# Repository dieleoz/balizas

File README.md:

# Baliza — Señal Vial «30 CUANDO ACTIVADA» (v3.3)

Control inteligente de la **luz intermitente de una señal de tránsito** instalada frente a zonas escolares.
Cuando la luz titila a **1.0 Hz** (500 ms ON / 500 ms OFF), el límite de **30 km/h está vigente legalmente**. El resto del día la señal permanece apagada.

El horario en el que debe titilar **está grabado físicamente en la placa metálica de la señal**:
* **Mañana:** 06:00 am a 09:00 am
* **Mediodía:** 11:30 am a 01:30 pm (13:30)
* **Tarde:** 03:00 pm (15:00) a 04:30 pm (16:30)

---

## 🏗️ Arquitectura del Sistema

```mermaid
flowchart LR
    APP["📱 App Android<br/>IT VIAL 30 v3.3<br/>Baliza_v3.3.apk"] -->|"Bluetooth SPP 9600 8N1<br/>Tramas ¿...?"| BT["Módulo Bluetooth<br/>JDY-31 / SIG0109A"]
    BT -->|"RC6 TX · RC7 RX"| PIC["PIC18F2550 (C99)<br/>Flash: 53.1% · RAM: 27.7%"]
    RTC["DS1307 + Pila CR2032<br/>Hora, Fecha y Calendario"] <-->|"I2C (Anti-Bloqueo)"| PIC
    PIC -->|"LATC2"| LUZ["💡 Foco Ámbar (1.0 Hz)"]
    PIC -->|"LATC1"| BUZ["Buzzer"]
    PIC -->|"AN1 (ADC)"| BAT["🔋 Batería 12V / Panel"]
    PIC -->|"0x00-0x5F"| EE["💾 EEPROM (Alarmas, Cortes, Nombre OTA)"]
```

## La v3.3 es una pareja, y solo vale junta

**La v3.3 son dos ficheros que se probaron juntos contra una señal real.** Confirmado por el
responsable el 22-ago-2026. No se mezclan con nada de otra procedencia:

| | Fichero | Tamaño | SHA-256 |
|---|---|---|---|
| **Firmware** | [`1 Firmware/Doc mplabx/build_xc8/main.hex`](1%20Firmware/Doc%20mplabx/build_xc8/main.hex) | 59.577 B | `c14b4350d960ce46c716d398f357acdee21f05660ef47c0ea61a7d513b8539c5` |
| **App** | [`1 Firmware/Baliza_v3.3.apk`](1%20Firmware/Baliza_v3.3.apk) | 3.859.625 B | `9c37d599deb995b0fa606d65b5e7fa7e813a08314535f9ba1959b3524d391a87` |

> ### ⚠️ Hay otro `.hex` con nombre de entregable que NO es este
>
> `BALIZA_18F2550_V1_CORREGIDO.hex` —tanto el de `1 Firmware/` como **el que hay dentro de
> `Release_v3.3/Binarios/`**— es un binario **distinto**: 49.068 B, `048856fc…`. No es el que
> funcionó. El nombre engaña justo donde más caro sale, porque está dentro de la carpeta de
> release y cualquiera lo tomaría por el bueno. **Antes de grabar, se comprueba el SHA-256, no
> el nombre del fichero.**

| Parámetro | Valor |
|---|---|
| **Microcontrolador** | **Microchip PIC18F2550** a 20.0 MHz (HS) |
| **Compilador Firmware** | **C99** (`--std=c99`). ⚠️ **La versión exacta de XC8 de este binario no está registrada**: la carpeta `build_xc8/` no conserva el `.map`. Ver ROADMAP, pendiente 5 |
| **Binario que corre HOY en la calle** | Sin confirmar — ver ROADMAP, pendiente 3 |
| **Cobertura de Pruebas** | **78 de 78 · PASS**, medido el **22-ago-2026** con `python "4 Simulador/correr.py"` |
| **Comprobación de interfaz** | **PASS** — contraste WCAG, áreas táctiles, responsive y **controles muertos**, con `comprobar_ui.py`. **No sustituye a verla en un teléfono** |

---

## Las mejoras de hoy: candidatas a la proxima version

Sobre la v3.3 hay **40 commits del 22-ago-2026** con trabajo real: saneamiento de la ISR,
aritmetica de punto fijo en vez de float, timeouts en I2C y UART, telemetria de bateria,
contador de cortes, nombre por el aire (OTA), autodiagnostico en la App y exportacion del
certificado. De ahi salen otros dos binarios:

| | Fichero | Tamano | SHA-256 (12) |
|---|---|---|---|
| Firmware | `1 Firmware/BALIZA_18F2550_V1_CORREGIDO.hex` | 49.201 B | `61e0441df8ce` |
| App | `7 sw apk/Baliza_IT_VIAL_30_v3.4.apk` | 4.570.283 B | `9864125aba51` |

**Son la base de la proxima version, no una version.** Tres cosas tienen que pasar antes de
que puedan llamarse v3.4 y salir a campo:

1. **Funcional tiene que revisar las funciones nuevas.** Ninguna lo ha hecho todavia.
2. ~~Incrementar el `versionCode`.~~ **HECHO el 22-ago-2026.** `build.gradle` esta en
   `versionCode 34` / `versionName "3.4"` y el APK se **recompilo**, asi que ahora se declara
   de verdad como 3.4 y Android si ofrece la actualizacion sobre una v3.3 instalada.
   (El tamano del APK varia entre compilaciones sin que cambie el contenido: es solo
   compresion. Comparar el contenido, no el tamano.)
3. **Hay que probar la pareja junta contra una senal real**, como se hizo con la v3.3. El
   firmware nuevo y la App nueva no se han validado juntos en campo.

Mientras tanto, **lo que se instala en campo es la v3.3**, y las dos cosas no se mezclan: la
App v3.3 con el `.hex` de la v3.3.

## Funcionalidades de la v3.3

Segun `Release_v3.3/LEEME_RELEASE_v3.3.md`, la v3.3 lleva:

**Firmware** (`main.hex`, 59.577 B)

1. **Cadencia reglamentaria de 1.0 Hz** - 500 ms encendido / 500 ms apagado.
2. **Mapeo de pines corregido:** buzzer en `RC1`, foco LED en `RC2`, pulsador en `RC0`.
3. **Parser serie protegido** contra tramas truncadas y caracteres NUL.
4. **Telemetria de bateria 12 V** por el canal ADC `AN1`.
5. **Contador de cortes de energia en EEPROM** (`0x36-0x37`).

**App** (`Baliza_v3.3.apk`, 3.859.625 B)

6. **1-Toque** que graba tres franjas FIJAS (06:00-09:00, 11:30-13:30, 15:00-16:30 L-V) — las de un colegio concreto. Sustituido en la candidata por la tarjeta «Horario de esta placa».
7. **Test de luz de 2 minutos** a 1.0 Hz con apagado rapido.
8. **Tema oscuro de alto contraste** para visibilidad diurna bajo sol.

> **Lo que NO esta en la v3.3:** el nombre por el aire (OTA), el certificado por WhatsApp y el
> semaforo de autodiagnostico. Esas son funciones de la compilacion de trabajo llamada «v3.4»
> y **no han pasado por funcional**. Si algun manual las describe como disponibles, el manual
> va por delante de lo aprobado.

---

## 🧪 Pruebas, Simulación y Emulador Web

Para verificar la compuerta de calidad o correr el simulador interactivo:

```bash
# 1. Arnés de 58 pruebas unitarias, estrés de 100k ciclos y 6 meses continuos:
python "4 Simulador/correr.py"

# 2. Suite automatizada End-to-End paso a paso (Headless):
python "4 Simulador/test_suite_e2e.py"

# 3. Emulador Web Interactivo conectado al Microcontrolador en C:
python "4 Simulador/servidor_interactivo.py"
# Abrir en el navegador: http://localhost:8080
```

---

### Qué NO cubren esas comprobaciones

El arnés compila los `.c` reales del firmware y los ejercita en el PC, pero **no toca un solo
pin**. Verde aquí no es entregable y no autoriza a grabar. En concreto no dice nada de:

* **El ADC.** Desde el 22-ago-2026 **sí lo cubre en parte** (bloque `I` del arnés), y lo
  primero que midió es que **la baliza no mide la temperatura**: el estado que la lee es
  código muerto, nadie transiciona a él. **La telemetría de batería (`AN1`) no está afectada
  y funciona.** Detalle en [`ROADMAP.md`](ROADMAP.md).
* **El I²C y el DS1307.** El reloj simulado siempre responde. Una pila `CR2032` agotada o unas
  pull-ups mal no existen en el simulador.
* **Que el módulo Bluetooth empareje.** Al arnés se le meten las tramas directamente.
* **Que el horario grabado coincida con la chapa atornillada a esa señal.** Esto es lo que más
  importa y **solo lo puede comprobar una persona con la señal delante**.

---

## 📚 Documentación Oficial y Manuales

* 📱 **Instalador de campo (v3.3, el aprobado):** [`1 Firmware/Baliza_v3.3.apk`](1%20Firmware/Baliza_v3.3.apk)
* 🔧 **Compilacion de trabajo (NO aprobada):** [`7 sw apk/Baliza_IT_VIAL_30_v3.4.apk`](7%20sw%20apk/Baliza_IT_VIAL_30_v3.4.apk)
* 🔧 **Compilar la app (cadena, dependencias, trampas):** [`Manuales/COMPILAR_APP.md`](Manuales/COMPILAR_APP.md)
* 📖 **Manual de Usuario de la App:** [`Manuales/MANUAL_USUARIO_APP.md`](Manuales/MANUAL_USUARIO_APP.md)
* ⚙️ **Manual Técnico del Firmware C99:** [`Manuales/MANUAL_TECNICO_FIRMWARE_C99.md`](Manuales/MANUAL_TECNICO_FIRMWARE_C99.md)
* 📜 **Certificado Oficial de Calibración y Pruebas:** [`Manuales/CERTIFICADO_FIRMWARE_v3.4.md`](Manuales/CERTIFICADO_FIRMWARE_v3.4.md)
* 🗺️ **Gestión de Múltiples Señales y Nombres OTA:** [`Manuales/GESTION_MULTISEÑALES_Y_NOMBRES.md`](Manuales/GESTION_MULTISE%C3%91ALES_Y_NOMBRES.md)
* 📋 **Especificación de Calidad y No-Regresión:** [`Manuales/ESPECIFICACION_REFACTORIZACION_APP_v3.4.md`](Manuales/ESPECIFICACION_REFACTORIZACION_APP_v3.4.md)
* 🩺 **Guía de Diagnóstico y Logs de Soporte:** [`Manuales/GUIA_DIAGNOSTICO_Y_LOGS_SOPORTE.md`](Manuales/GUIA_DIAGNOSTICO_Y_LOGS_SOPORTE.md)
* 🏛️ **Dictamen del Comité Técnico:** [`Manuales/DICTAMEN_COMITE_TECNICO_MULTIDISCIPLINARIO.md`](Manuales/DICTAMEN_COMITE_TECNICO_MULTIDISCIPLINARIO.md)
* ⚖️ **Base normativa (Manual de Señalización Vial):** [`Manuales/NORMATIVA.md`](Manuales/NORMATIVA.md)
* 🗺️ **Hoja de Ruta (Roadmap):** [`ROADMAP.md`](ROADMAP.md)

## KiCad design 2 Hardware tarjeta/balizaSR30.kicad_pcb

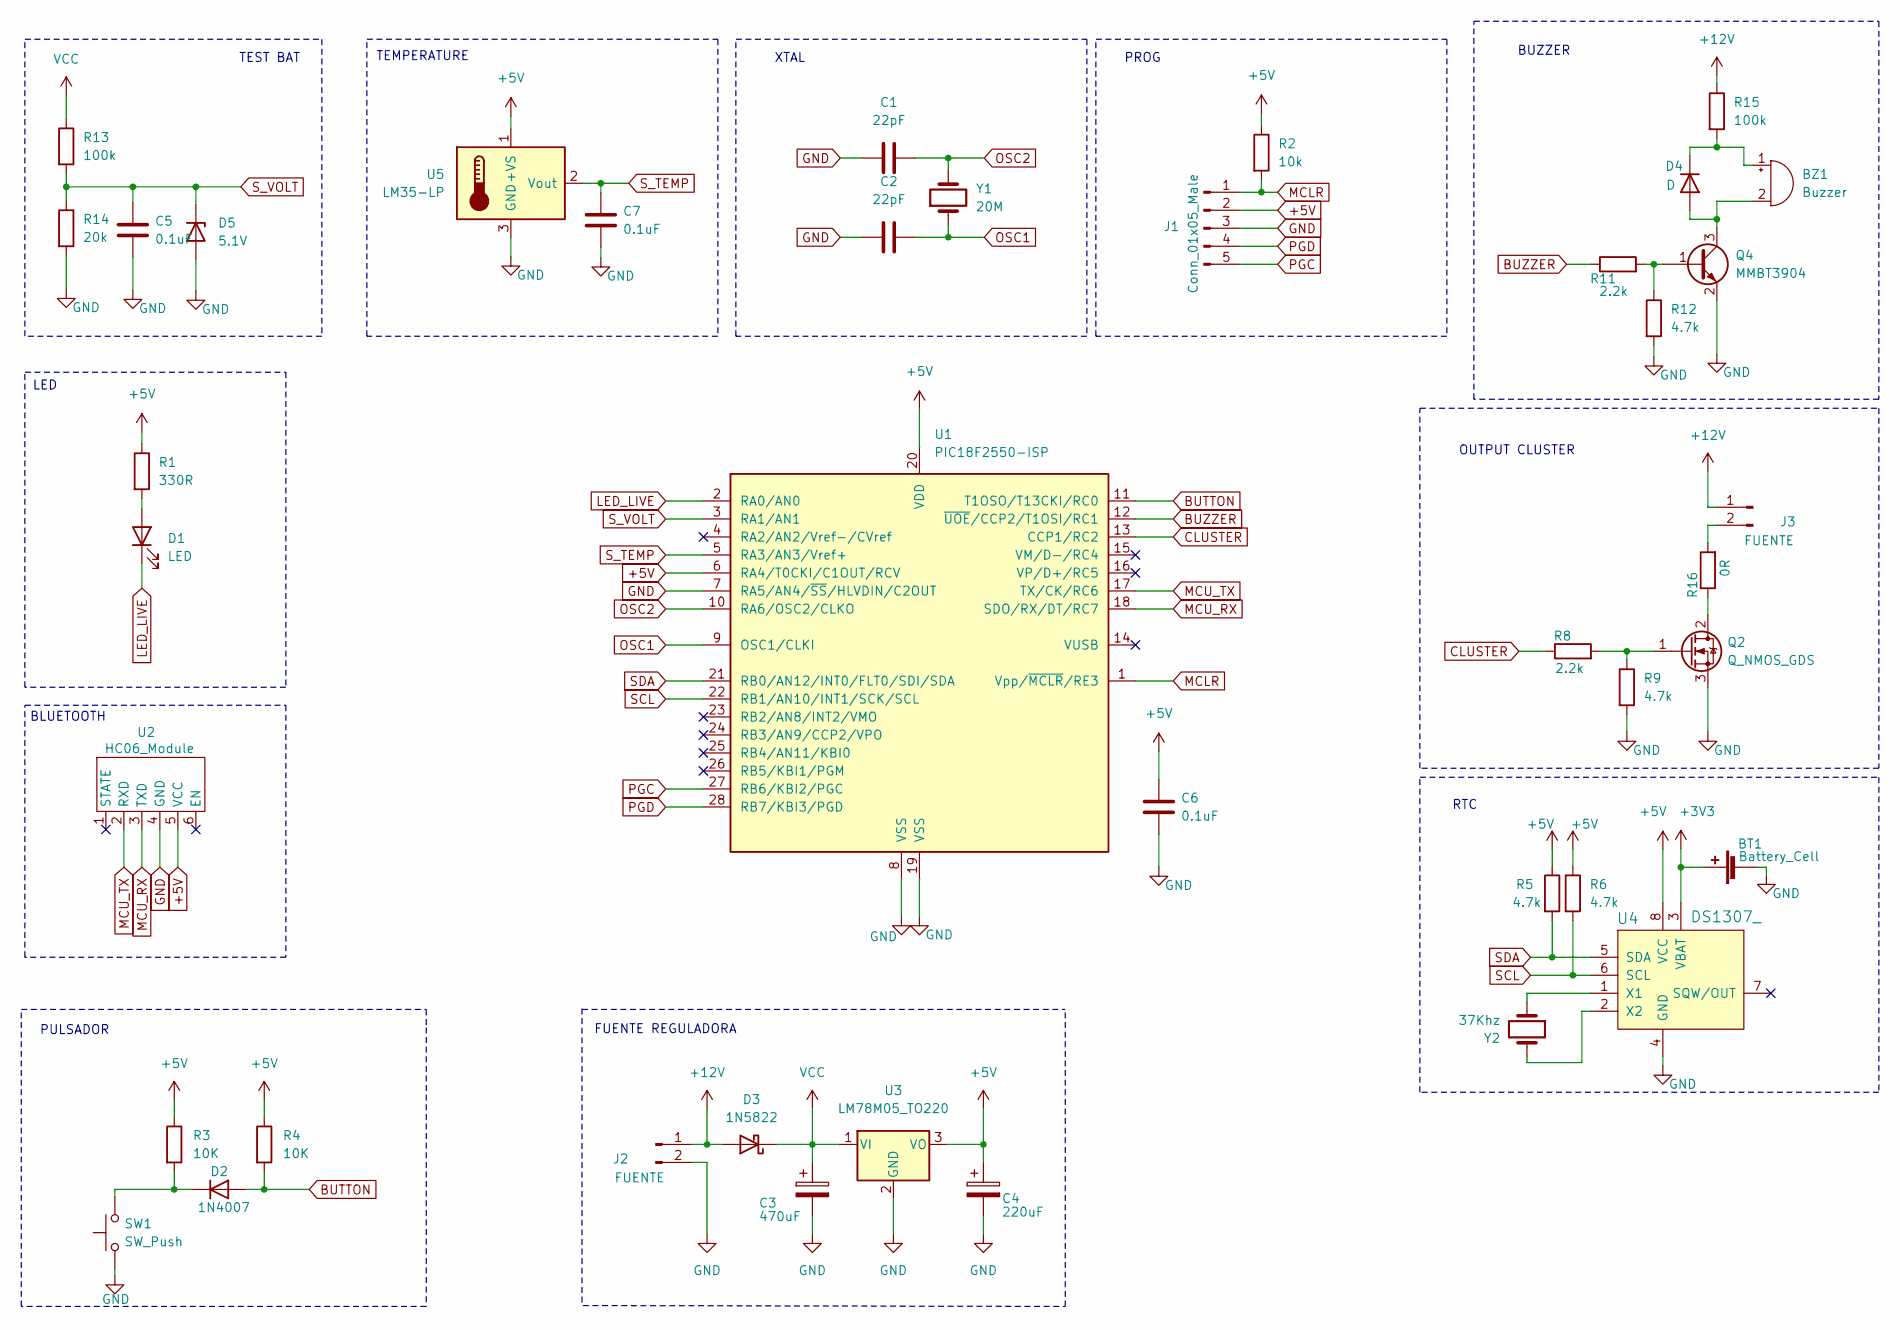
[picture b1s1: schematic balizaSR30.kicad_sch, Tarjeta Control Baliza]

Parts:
BT1: Battery_Cell; BatteryHolder_Keystone_103_1x20mm
BZ1: Buzzer; Buzzer_12x9.5RM7.6
C1, C2: 22pF; C_0805_2012Metric
C3: 470uF; CP_Radial_D8.0mm_P2.50mm
C4: 220uF; CP_Radial_D8.0mm_P2.50mm
C5, C6, C7: 0.1uF; C_0805_2012Metric
D1: LED; LED_D3.0mm
D2: 1N4007; D_DO-41_SOD81_P7.62mm_Horizontal
D3: 1N5822; D_DO-201AD_P15.24mm_Horizontal
D4: D; D_A-405_P7.62mm_Horizontal
D5: 5.1V; D_DO-34_SOD68_P7.62mm_Horizontal
J1: Conn_01x05_Male; PinHeader_1x05_P2.54mm_Vertical
J2, J3: FUENTE; Molex_KK-396_5273-02A_1x02_P3.96mm_Vertical
Q2: Q_NMOS_GDS; TO-220-3_Horizontal_TabDown
Q4: MMBT3904; SOT-23
R1: 330R; R_1206_3216Metric
R2: 10k; R_1206_3216Metric
R3, R4: 10K; R_1206_3216Metric
R5, R6, R9, R12: 4.7k; R_1206_3216Metric
R8, R11: 2.2k; R_1206_3216Metric
R13, R15: 100k; R_1206_3216Metric
R14: 20k; R_1206_3216Metric
R16: 0R; R_2010_5025Metric
SW1: SW_Push; SW_PUSH_6mm_H4.3mm
U1: PIC18F2550-ISP; DIP-28_W7.62mm
U2: HC06_Module; HC06
U3: LM78M05_TO220; TO-220-3_Horizontal_TabDown
U4: DS1307_; DIP-8_W7.62mm; MPN DS1307+; Digi-Key_PN DS1307+-ND
U5: LM35-LP; TO-92L_Inline_Wide
Y1: 20M; Crystal_HC18-U_Vertical
Y2: 37Khz; Crystal_AT310_D3.0mm_L10.0mm_Horizontal

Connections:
+3V3: BT1.1 (+), U4.3 (VBAT)
+5V: C4.1, C6.1, J1.2, R1.1, R2.1, R3.1, R4.1, R5.1, R6.1, U1.6 (RA4/T0CKI/C1OUT/RCV), U1.20 (VDD), U2.5 (VCC), U3.3 (VO), U4.8 (VCC), U5.1 (+VS)
+12V: D3.2 (A), J2.1, J3.1, R15.1
BUTTON: D2.2 (A), R4.2, U1.11 (T1OSO/T13CKI/RC0)
BUZZER: R11.1, U1.12 (~UOE/CCP2/T1OSI/RC1)
CLUSTER: R8.1, U1.13 (CCP1/RC2)
GND: BT1.2 (-), C1.1, C2.1, C3.2, C4.2, C5.2, C6.2, C7.2, D5.2 (A), J1.3, J2.2, Q2.3 (S), Q4.2 (E), R9.2, R12.2, R14.2, SW1.1, U1.7 (RA5/AN4/~SS/HLVDIN/C2OUT), U1.8 (VSS), U1.19 (VSS), U2.4 (GND), U3.2 (GND), U4.4 (GND), U5.3 (GND)
LED_LIVE: D1.1 (K), U1.2 (RA0/AN0)
MCLR: J1.1, R2.2, U1.1 (Vpp/~MCLR/RE3)
MCU_RX: U1.18 (SDO/RX/DT/RC7), U2.3 (TXD)
MCU_TX: U1.17 (TX/CK/RC6), U2.2 (RXD)
unnamed: BZ1.2 (+), D4.2 (A), Q4.3 (C)
unnamed: BZ1.1 (-), D4.1 (K), R15.2
unnamed: D1.2 (A), R1.2
unnamed: D2.1 (K), R3.2, SW1.2
unnamed: J3.2, R16.2
unnamed: Q2.2 (D), R16.1
unnamed: Q2.1 (G), R8.2, R9.1
unnamed: Q4.1 (B), R11.2, R12.1
unnamed: U4.1 (X1), Y2.1
unnamed: U4.2 (X2), Y2.2
OSC1: C2.2, U1.9 (OSC1/CLKI), Y1.1
OSC2: C1.2, U1.10 (RA6/OSC2/CLKO), Y1.2
PGC: J1.5, U1.27 (RB6/KBI2/PGC)
PGD: J1.4, U1.28 (RB7/KBI3/PGD)
SCL: R6.2, U1.22 (RB1/AN10/INT1/SCK/SCL), U4.6 (SCL)
SDA: R5.2, U1.21 (RB0/AN12/INT0/FLT0/SDI/SDA), U4.5 (SDA)
S_TEMP: C7.1, U1.5 (RA3/AN3/Vref+), U5.2 (Vout)
S_VOLT: C5.1, D5.1 (K), R13.2, R14.1, U1.3 (RA1/AN1)
VCC: C3.1, D3.1 (K), R13.1, U3.1 (VI)

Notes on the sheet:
LED
OUTPUT CLUSTER
FUENTE REGULADORA
PROG
BUZZER
BLUETOOTH
XTAL
RTC
TEMPERATURE
PULSADOR
TEST BAT

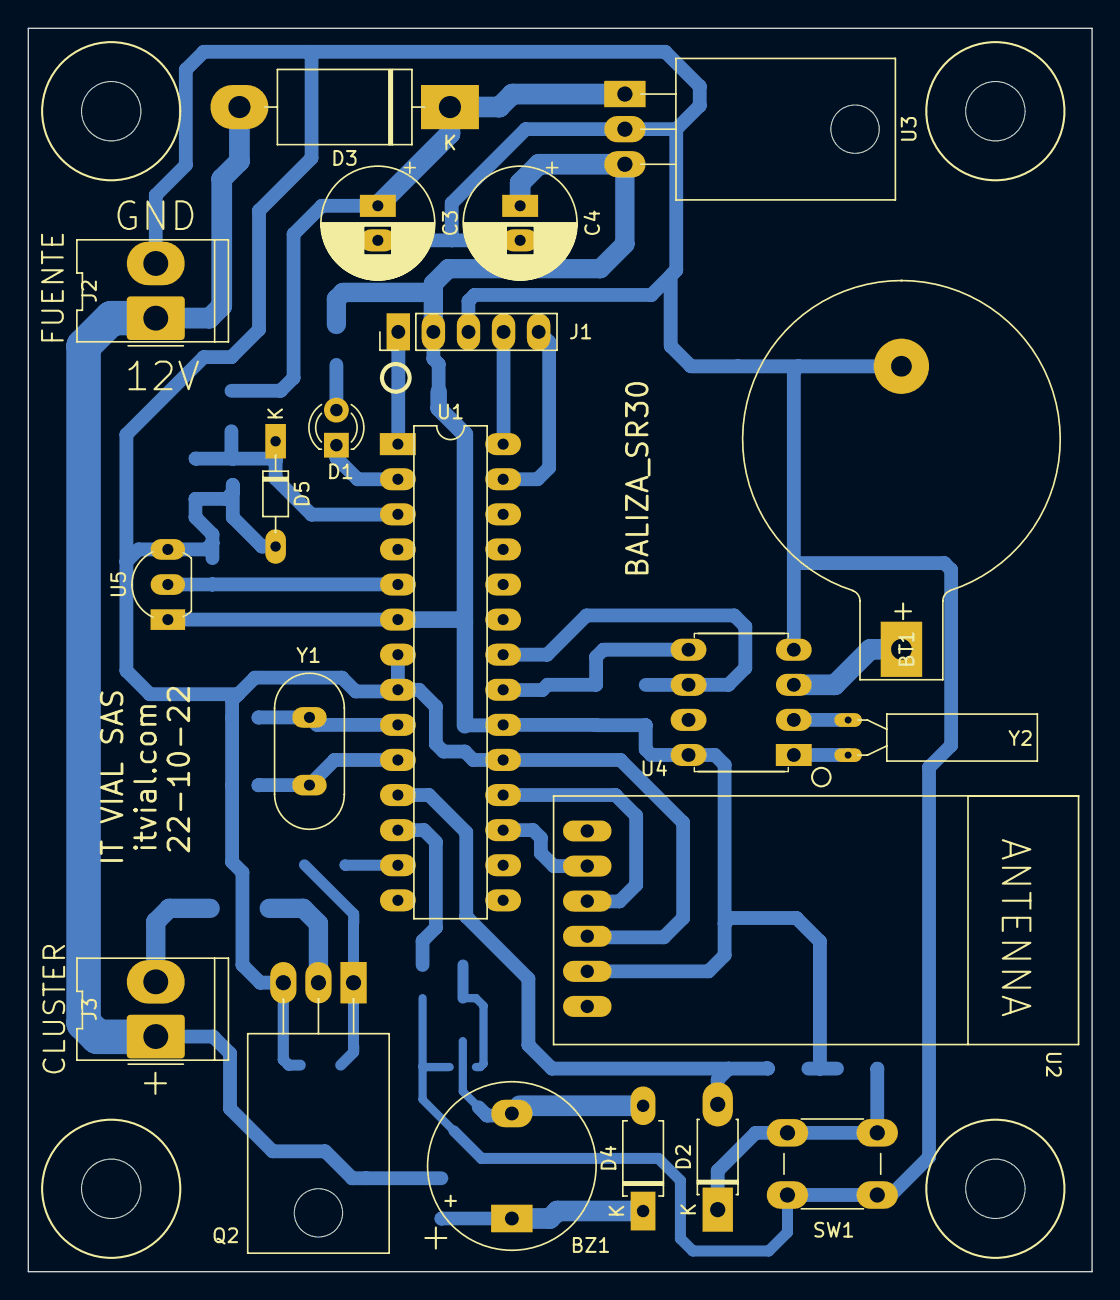
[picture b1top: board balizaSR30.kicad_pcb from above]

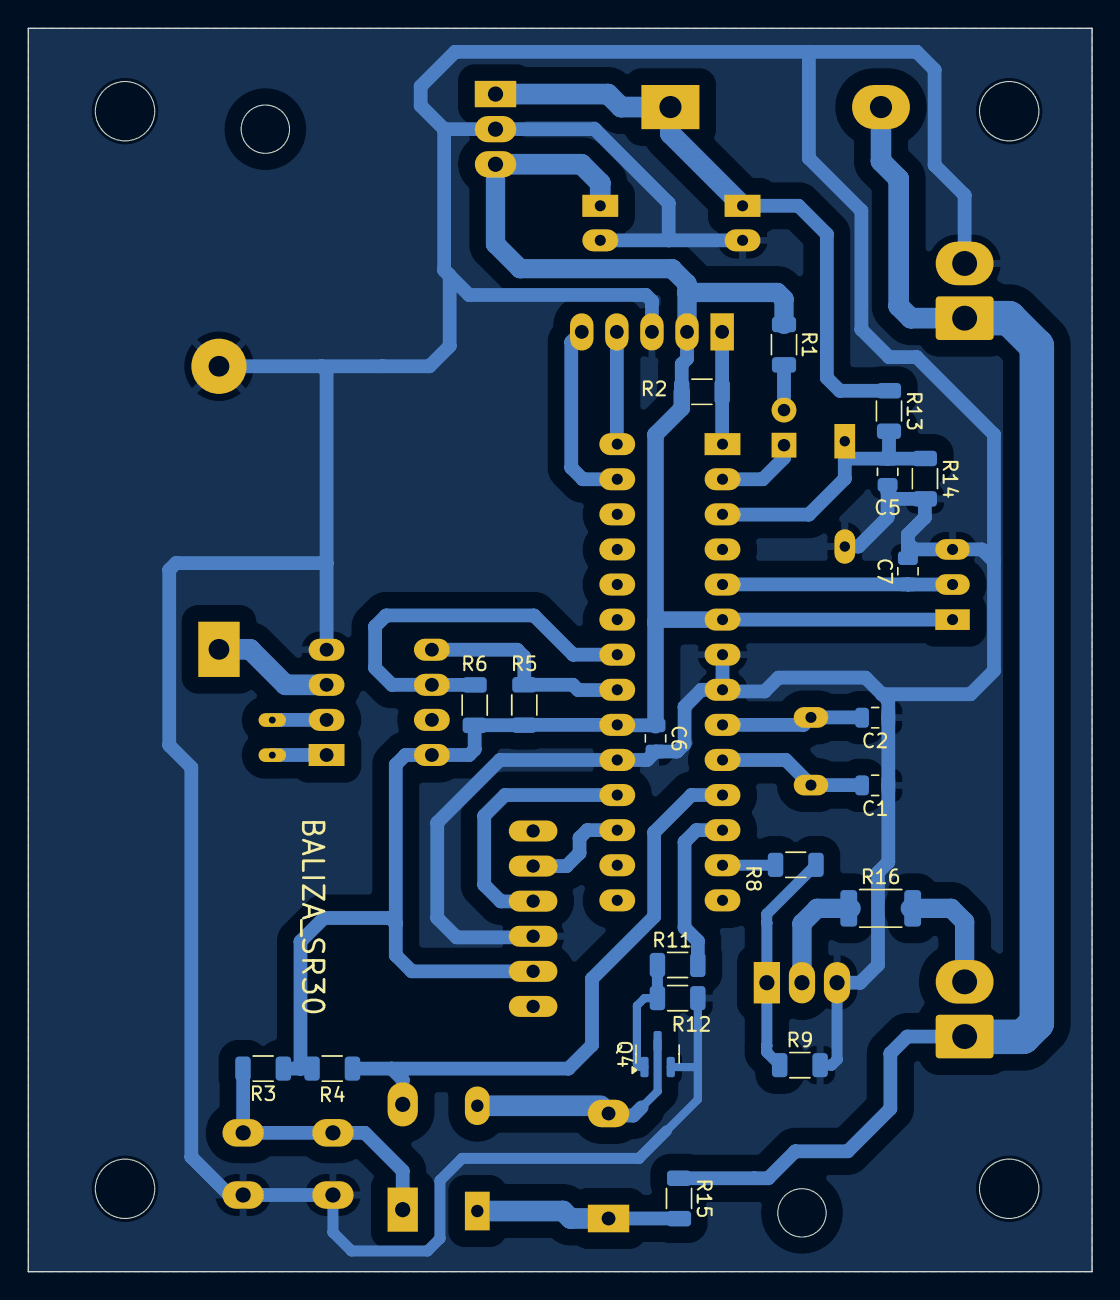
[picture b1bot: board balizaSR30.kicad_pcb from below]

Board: 2 copper layers, 77.0 x 90.0 mm, 41 parts (20 on the bottom side), 30 nets.
